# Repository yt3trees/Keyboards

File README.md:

# Limb44
Limb44, a split keyboard with 3x6 column staggered keys and 4 thumb keys.

# Beryl32
Beryl32, a keyboard with 3x10 column staggered keys and 2 thumb keys.

Keyboard Maintainer: [yt3trees](https://github.com/yt3trees/)  [@yt3trees](https://twitter.com/yt3trees)
Firmware: [keyboards/limb44](https://github.com/yt3trees/qmk_firmware/tree/master/keyboards/limb44)

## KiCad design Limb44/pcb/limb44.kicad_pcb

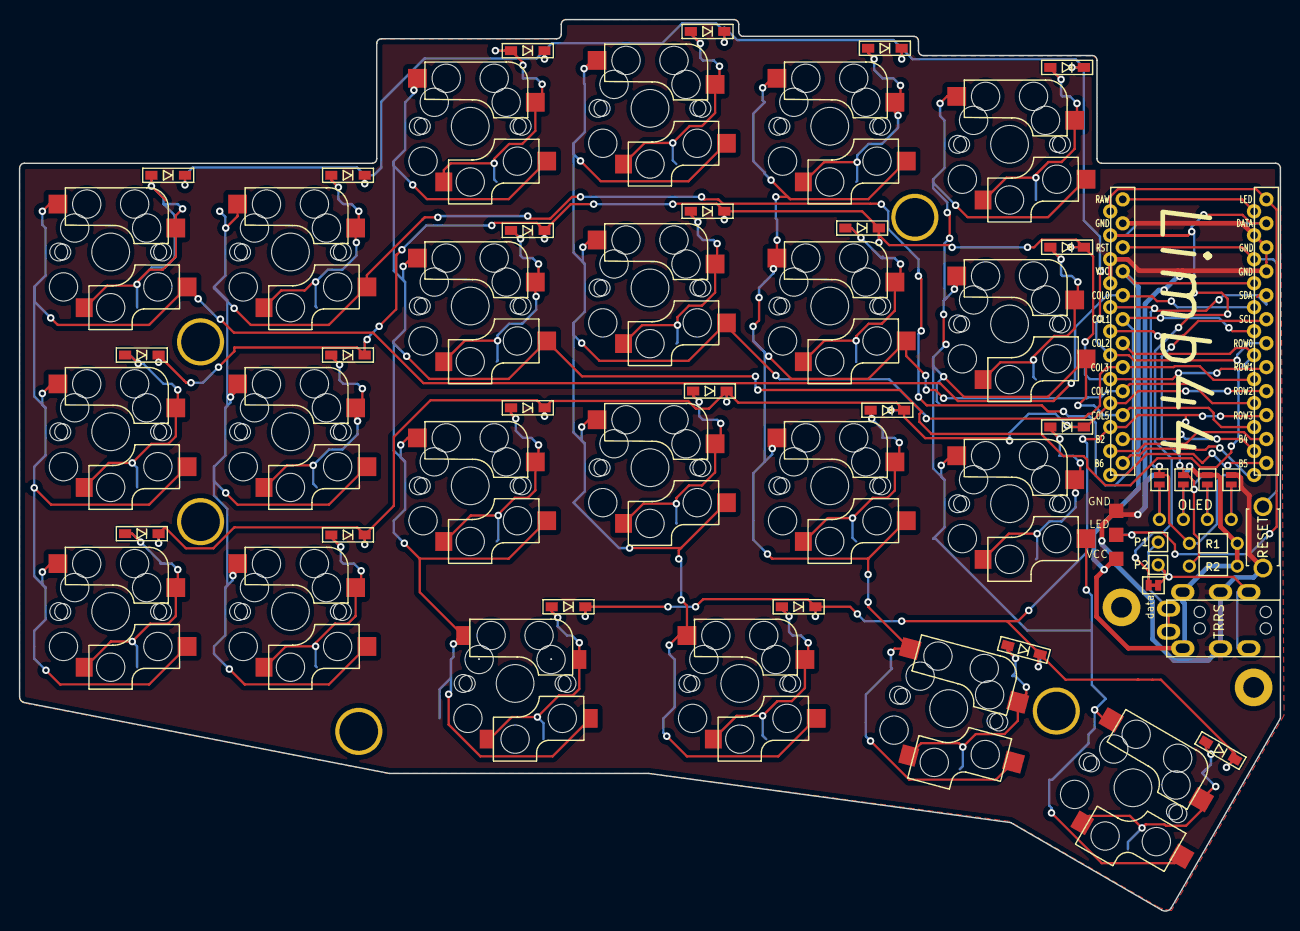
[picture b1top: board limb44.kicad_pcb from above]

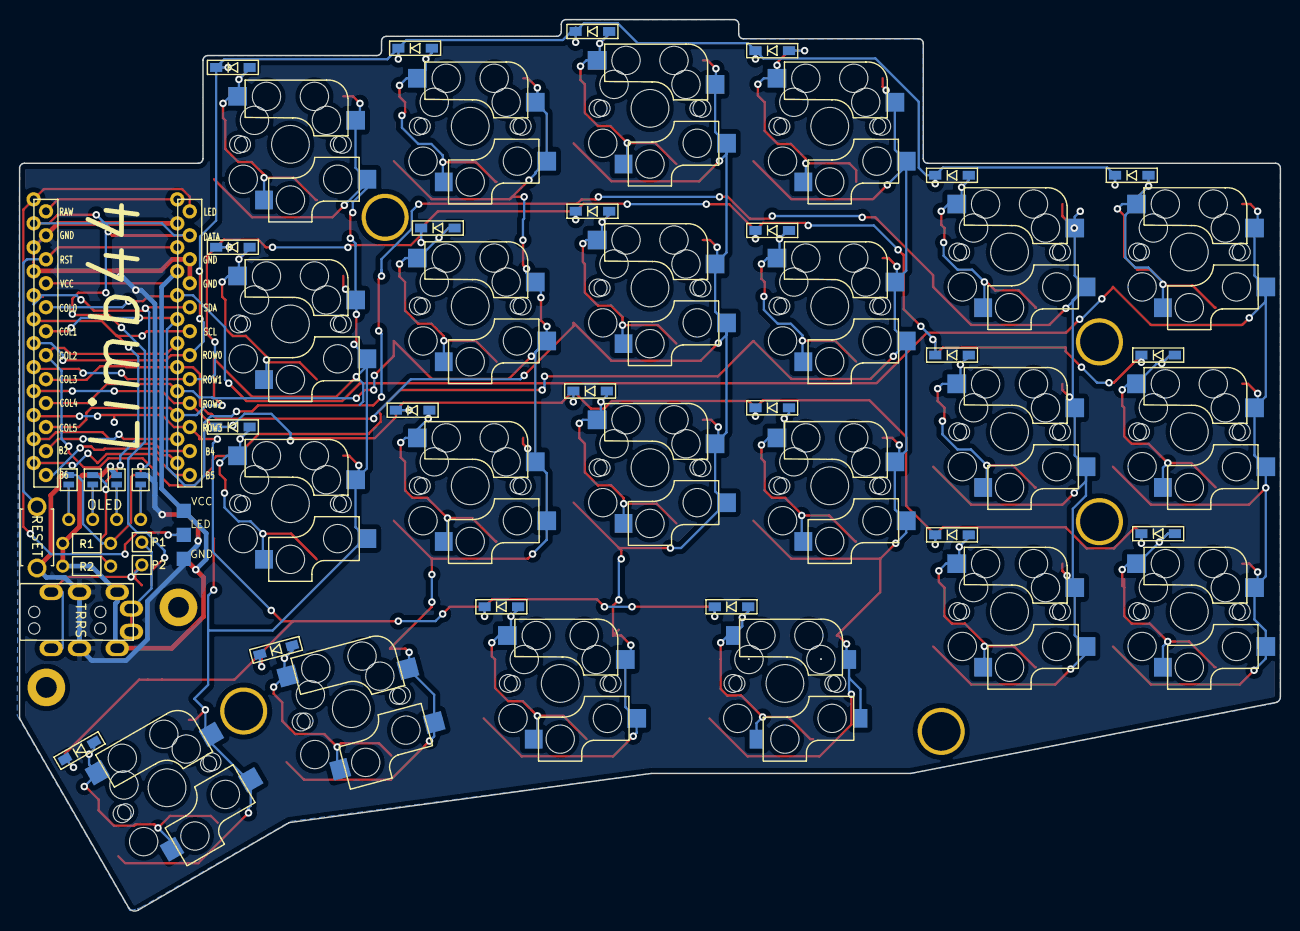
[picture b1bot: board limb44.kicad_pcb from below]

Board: 2 copper layers, 133.6 x 94.5 mm, 69 parts (4 on the bottom side), 45 nets.

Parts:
D1, D2, D3, D4, D5, D6, D7, D8, D9, D10, D11, D12, D13, D14, D15, D16, D17, D18, D19, D20, D21, D22: D; D3_SMD
J1: MJ-4PP-9
J2: LED; StripLED_rev
J5: OLED; OLED_v2
JP1: Jumper; JPC2
JP2, JP3, JP4, JP5, JP6, JP7, JP8, JP9: Jumper_NO_Small; Jumper
P1, P2: i2c-pin; 1pin_conn
R1, R2: R
RSW1: RESET_SWITCH; ResetSW
Ref**: Val**; HOLE
Ref**#2, Ref**#3, Ref**#4, Ref**#5, Ref**#6, Ref**#7: Val**; HOLE
SW1, SW2, SW3, SW4, SW5, SW6, SW7, SW8, SW9, SW10, SW11, SW12, SW13, SW14, SW15, SW16, SW17, SW18, SW20, SW21, SW22: SW_PUSH; CherryMX_Choc_Hotswap
SW19: SW_PUSH; CherryMX_Choc_Hotswap_1.5u
U1: ProMicro; ProMicro_v2

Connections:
GND: J1.C, J2.1, JP2.2, JP9.2, RSW1.2, U1.3, U1.4, U1.23
unnamed: D1.2, SW1.2
unnamed: D2.2, SW2.2
unnamed: D3.2, SW3.2
unnamed: D4.2, SW4.2
unnamed: D5.2, SW5.2
unnamed: D6.2, SW6.2
unnamed: D7.2, SW7.2
unnamed: D8.2, SW8.2
unnamed: D9.2, SW9.2
unnamed: D10.2, SW10.2
unnamed: D11.2, SW11.2
unnamed: D12.2, SW12.2
unnamed: D13.2, SW13.2
unnamed: D14.2, SW14.2
unnamed: D15.2, SW15.2
unnamed: D16.2, SW16.2
unnamed: D17.2, SW17.2
unnamed: D18.2, SW18.2
unnamed: D19.2, SW19.2
unnamed: D20.2, SW20.2
unnamed: D21.2, SW21.2
unnamed: D22.2, SW22.2
unnamed: J1.A, P1.1
unnamed: J1.B, JP1.2, P2.1
unnamed: J5.1, JP5.1, JP9.1
unnamed: J5.2, JP4.1, JP8.1
unnamed: J5.3, JP3.1, JP7.1
unnamed: J5.4, JP2.1, JP6.1
VCC: J1.D, J2.3, JP3.2, JP8.2, R1.1, R2.1, U1.21
col0: SW1.1, SW7.1, SW13.1, U1.20
col1: SW2.1, SW8.1, SW14.1, U1.19
col2: SW3.1, SW9.1, SW15.1, SW19.1, U1.18
col3: SW4.1, SW10.1, SW16.1, SW20.1, U1.17
col4: SW5.1, SW11.1, SW17.1, SW21.1, U1.16
col5: SW6.1, SW12.1, SW18.1, SW22.1, U1.15
data: JP1.1, U1.2
led: J2.2, U1.1
reset: RSW1.1, U1.22
row0: D1.1, D2.1, D3.1, D4.1, D5.1, D6.1, U1.7
row1: D7.1, D8.1, D9.1, D10.1, D11.1, D12.1, U1.8
row2: D13.1, D14.1, D15.1, D16.1, D17.1, D18.1, U1.9
row3: D19.1, D20.1, D21.1, D22.1, U1.10
scl: JP4.2, JP7.2, R2.2, U1.6
sda: JP5.2, JP6.2, R1.2, U1.5

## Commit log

2020-11-09 Update LICENSE
2020-11-09 コミット
2020-11-09 Readme update
2020-11-09 gitignore update
2020-11-09 add gerber
2020-11-23 update top plate
2020-12-13 plate V2
2021-02-27 アクリル積層
2021-03-21 update folder structure and add Beryl32
2021-03-27 add 注文データ
2021-07-11 add V2
